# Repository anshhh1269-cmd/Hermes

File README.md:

# HERMES-I2C 

## Why This Project Exists
Honestly, I just wanted to build a custom circuit board that was actually simple to put together, but still gave me endless possibilities without getting boring after a week. I wanted something way more interactive and personal, not like a sensor to measure humidity or temp cause that's kinda boring.

By putting a 6-axis motion sensor (accelerometer + gyroscope) and a neat little screen on a shared I2C highway, this single piece of hardware can become whatever I need it to be just by changing the code. If I'm playing a racing gamE, I can literally mount this board inside a 3D-printed steering wheel loop and physically tilt it to steer my car.

---

## How It Works

### 1. The Hardware Architecture
The board relies on three main active parts chatting over a shared **I2C communication bus**:

*   **The Brain (XIAO RP2040):** This is the main microcontroller. It handles the raw calculations and has built-in USB functionality. This means it can easily trick my PC into thinking it's a real keyboard, mouse, or gaming controller.
*   **The Sensor (LSM6DS3TR-C):** This is the high-precision 6-axis IMU tracking my physical movements. The accelerometer handles raw speed and direction shifts, while the gyroscope measures physical angles and tilt; I chosethis by looking at multiple datasheets for many types of sensors
*   **The Screen (0.96" OLED Module):** An SSD1306-driven display sharing the same data tracks. It prints live variables, movement graphs, or setup menus so I can see what mode the device is in without guessing.

---
## Bill of Materials (BOM)

Every part on this schematic uses standard surface-mount (SMD) footprints mapped directly to **LCSC Part Numbers**. This lets the automated pick-and-place robot arms at JLCPCB find the parts in their warehouse inventory and solder them onto the board automatically.

| Qty | Component Type | Value / Model | LCSC Part # | Mechanical Footprint | Designator |
| :--- | :--- | :--- | :--- | :--- | :--- |
| 1 | Microcontroller | Seeed Studio XIAO RP2040 | `C2915003` | SMD Castellated Pad Map | `U1` |
| 1 | 6-Axis Motion Sensor | LSM6DS3TR-C (STMicroelectronics) | `C967633` | LGA-14 (`2.5mm x 3mm`) | `U2` |
| 1 | Display Connector Socket | 4-Pin Female Header | `C2718488` | `1x04 2.54mm` Vertical | `J1` |
| 2 | I2C Pull-Up Resistors | 4.7kΩ | `C22843` | SMD `0603` (`1608 Metric`) | `R1, R2` |
| 2 | Noise-Filtering Capacitors | 0.1µF | `C14663` | SMD `0603` (`1608 Metric`) | `C1, C2` |

---

## Schematic Design and PCB

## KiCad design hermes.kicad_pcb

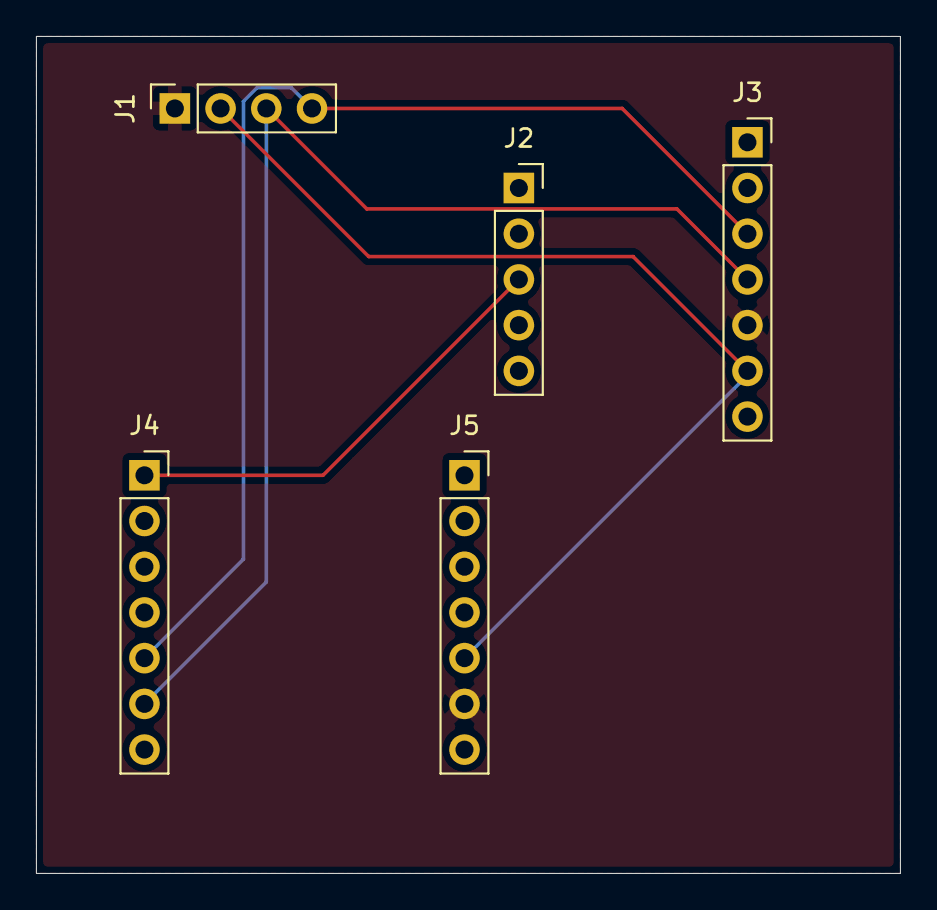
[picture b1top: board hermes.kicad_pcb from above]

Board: 2 copper layers, 48.0 x 46.5 mm, 5 parts (0 on the bottom side), 5 nets.

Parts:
J1: OLED Header; PinSocket_1x04_P2.54mm_Vertical
J2: sensor header 2; PinSocket_1x05_P2.54mm_Vertical
J3: sensor header 1; PinSocket_1x07_P2.54mm_Vertical
J4: XIAO header 1; PinSocket_1x07_P2.54mm_Vertical
J5: XIAO header 2; PinSocket_1x07_P2.54mm_Vertical

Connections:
/3V3: J1.2, J3.6, J5.5
/INT: J2.3 (Pin_3_3), J4.1
/SCL: J1.3, J3.4, J4.6
/SDA: J1.4, J3.3, J4.5
GND: J1.1, J3.5, J5.6
